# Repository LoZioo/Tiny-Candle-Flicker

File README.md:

# Tiny-Candle-Flicker
Basic candle flicker PCB and code built around an ATtiny13A

# Images

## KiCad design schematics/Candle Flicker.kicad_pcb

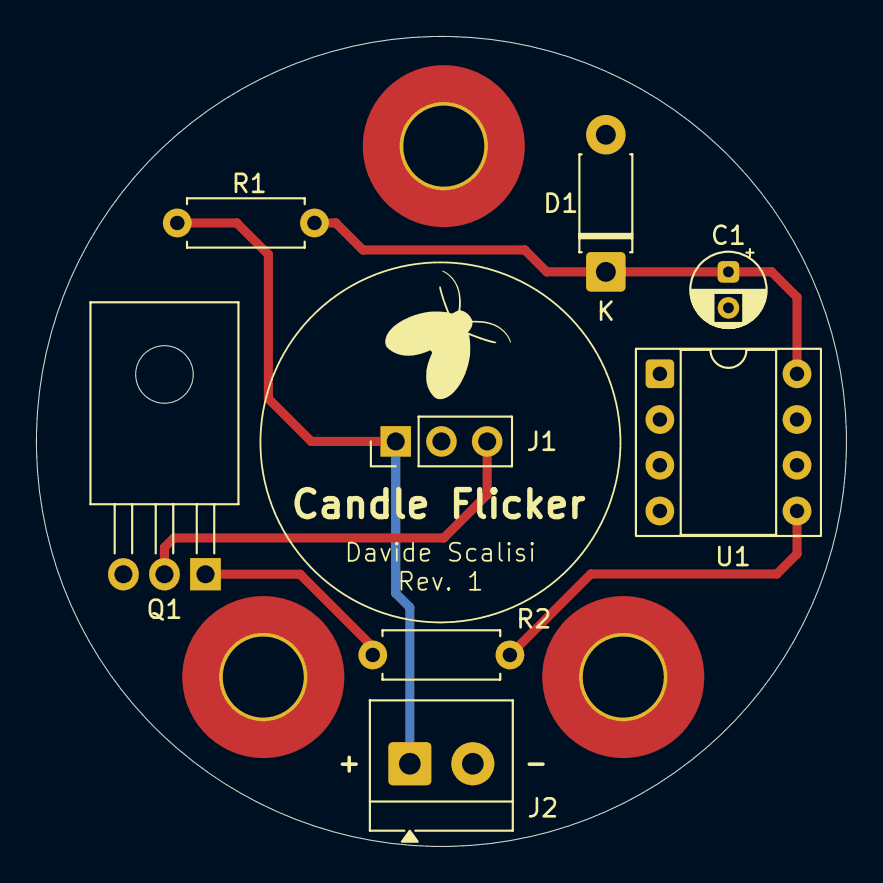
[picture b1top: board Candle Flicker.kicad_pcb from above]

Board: 2 copper layers, 45.0 x 45.0 mm, 11 parts (0 on the bottom side), 6 nets.

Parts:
C1: 10u; CP_Radial_D4.0mm_P2.00mm
D1: 3.1V; D_DO-41_SOD81_P7.62mm_Horizontal
H1, H2, H3: MountingHole; MountingHole_4.5mm_Pad_TopBottom
J1: Lamp; PinHeader_1x03_P2.54mm_Vertical
J2: Vin; TerminalBlock_4Ucon_1x02_P3.50mm_Horizontal
Q1: NPN; TO-126-3_Horizontal_TabUp
R1, R2: 220; R_Axial_DIN0207_L6.3mm_D2.5mm_P7.62mm_Horizontal
U1: ATtiny13A-P; DIP-8_W7.62mm_Socket

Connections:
+5V: C1.1, D1.1 (K), R1.2, U1.8 (VCC)
+12V: J1.1, J2.1, R1.1
GND: C1.2, D1.2 (A), J2.2, Q1.3 (E), U1.4 (GND)
unnamed: J1.3, Q1.2 (C)
unnamed: Q1.1 (B), R2.2
unnamed: R2.1, U1.5 (PB0)

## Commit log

2025-11-07 feat: schematics
2025-11-07 feat: added code
2025-11-07 docs
